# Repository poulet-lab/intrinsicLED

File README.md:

# intrinsicLED
 
# BOM (incomplete)
* https://octopart.com/16svpf1000m-panasonic-29498310
* https://octopart.com/dev-13305-sparkfun-66786787
* https://octopart.com/54-00129-tensility-96405015
* https://octopart.com/pec11r-4230k-s0024-bourns-82267986
* https://octopart.com/39502-1003-molex-655380
* https://octopart.com/39500-0003-molex-657436

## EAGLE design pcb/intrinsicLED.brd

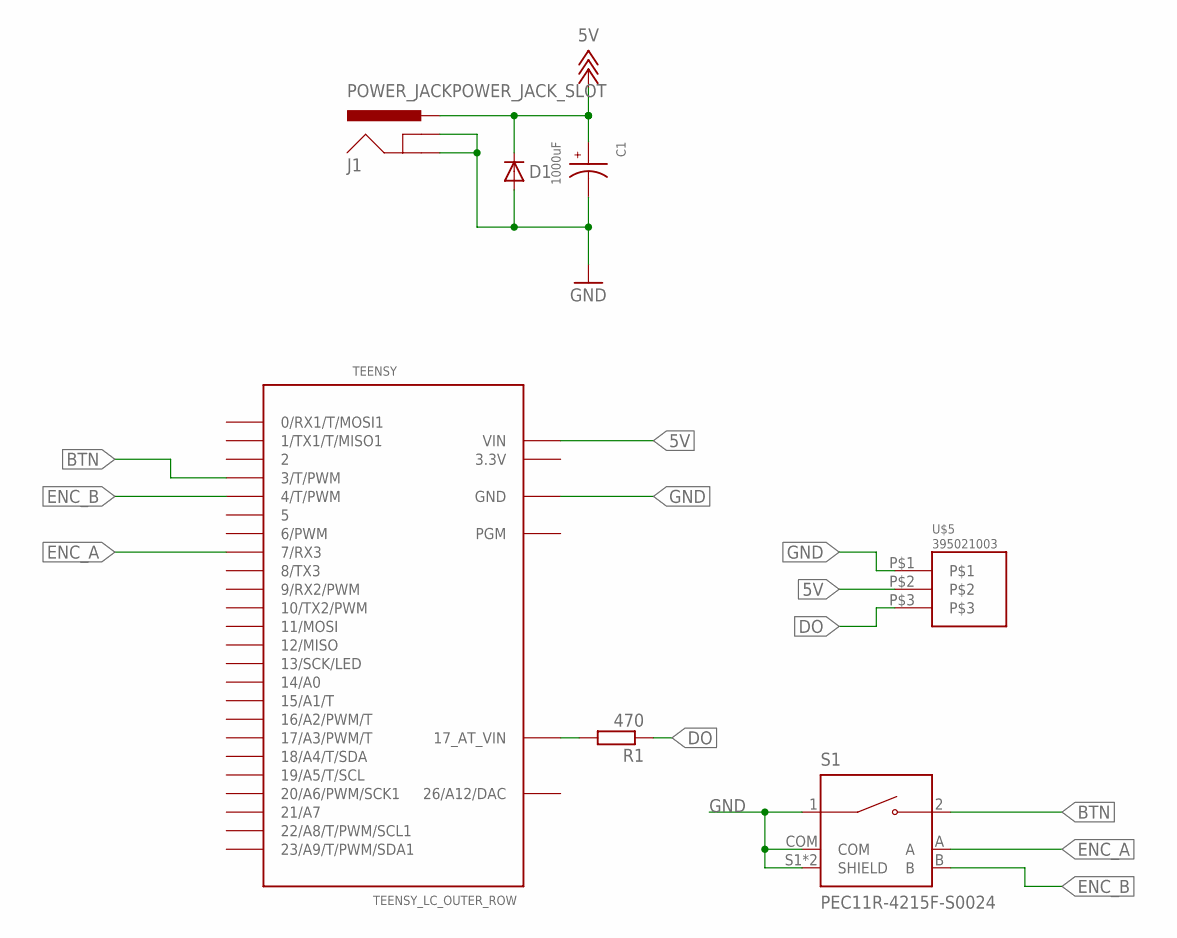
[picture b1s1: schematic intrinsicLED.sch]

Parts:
C1: 1000uF; CAP_16SVPF1000M
D1: DIODE-DO214AA; DO214AA
J1: POWER_JACKPOWER_JACK_SLOT; POWER_JACK_PTH_SLOT
R1: 470; R1206
S1: PEC11R-4215F-S0024; XDCR_PEC11R-4215F-S0024
TEENSY: TEENSY_LC_OUTER_ROW; TEENSY_3.0-3.2&LC_OUTER_ROW
U$5: 395021003

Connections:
3.3V: TEENSY.3.3V, TEENSY.3.3V1 (3.3V)
5V: C1.1, D1.C, J1.PWR, TEENSY.VIN, U$5.P$2
26/A12/DAC: TEENSY.RESET/DAC (26/A12/DAC)
BTN: S1.2, TEENSY.3 (3/T/PWM)
DO: R1.1, U$5.P$3
ENC_A: S1.A, TEENSY.7 (7/RX3)
ENC_B: S1.B, TEENSY.4 (4/T/PWM)
GND: C1.2, D1.A, J1.GND, J1.GNDBREAK, S1.1, S1.COM, S1.S1 (SHIELD), S1.S2 (SHIELD), TEENSY.AGND (GND), TEENSY.GND, TEENSY.GND1 (GND), U$5.P$1
unnamed: R1.2, TEENSY.VBAT (17_AT_VIN)

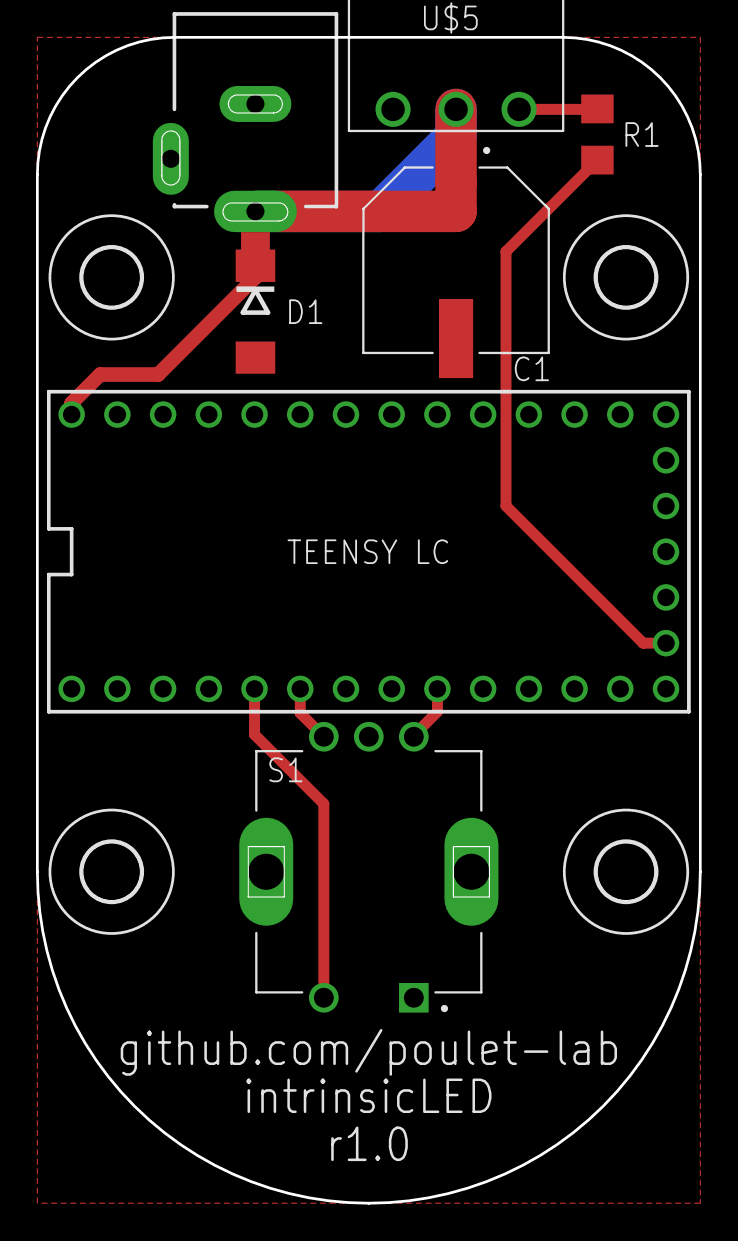
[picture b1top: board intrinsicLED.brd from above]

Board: 2 copper layers, 36.8 x 64.8 mm, 11 parts (0 on the bottom side), 8 nets.

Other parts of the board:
U$1, U$2, U$3, U$4: 3,2

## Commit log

2022-06-08 initial code
2022-06-08 PCB r1.0
2022-08-25 cleanup, added white mode
2022-08-25 implemented switching between WS2811 and NEOPIXEL chipsets
2022-08-25 limit maximum brightness of white mode
    to avoid overheating of the LED
2022-08-25 seperate increments for each mode
2022-09-02 add directional option for white mode

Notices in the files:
parts and their libraries:
SparkFun-Connectors: Licensing: Creative Commons ShareAlike 4.0 International - https://creativecommons.org/licenses/by-sa/4.0
